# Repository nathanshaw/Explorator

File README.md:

# Explorator Hardware

This repo contains the PCB layout and schematic files for the Explorator genus.

The files included in this repo were created within EAGLE CAD. 
## Repo Structure
PCB
- battery_pack
  - [18500](##Battery-Pack---18500)
  - [18650](##Battery-Pack---18650) 
- [breakout_board](##Explorator-Breakout-PCB)
- mainboard
  - [v1_large_pcb](##Explorator-v1-Mainboard-(large))
  - [v2_small_pcb](##Explorator-v2-Mainboard-(small))

### Repo Files
- .brd files are EAGLE's board files and contain information about the PCB's layout. 
- .sch files are EAGLE's schematic files and contain information about the schematic from which the PCB's are designed.
- .lbr files are EAGLE's library files and contain all the libraries used to create the individual PCB's, there should be a libary file for each folder in the repo. The entire libraries are exported for the battery pack and breakout PCB(including parts not in the design), but for the mainboards only the footprints used in the design are exported to save repo space.
- README.md files accompany each board in the appropiate folder and contains information about manufacturing the PCB, known issues, and other notes
- .png's are included for each board and include the schematic, and the layout of the board.
  - Files that start with "schematic_" are schematic images 
  - Files that start with "layout_" are layout images.
- parts_list.txt is a text file created by EAGLE showing the components used to populate each board. 
- pin_list.txt is a list of all the pin and pad names in the layout and schematic files
- BOM_*.csv is a comma separated list that contains all of the electronic components needed for the PCB (similar to parts_list.txt, but more useful most of the time)
- net_list.txt is a list of all the connections between different nets in the schematic
- CAMOutputs contains two folders, one for the drill file and one for the other gerbers. These outputs were created in EAGLE using the PCBWay_2_layer.cam file at the root level of the PCB folder

Please note, if you do not have access to EAGLE CAD, the easiest way to view these boards is by using an online gerber viewer such as this one provided by [pcbway.com!]<https://www.pcbway.com/project/OnlineGerberViewer.html>. To use this method simply .zip the CAMOutputs folder and drag the compressed .zip file into the browser and an interactive PCB generated from the Gerbers can be viewed. Pretty cool =)

# Repo Contents
The following PCB designs are included in this repo:

## Explorator v1 Mainboard (large)
    
- 99mm diameter
- Teensy 3.2 Microcontroller
- 1x SHTC3 Temperature and Humidity Sensor
- 3x channel of DC motor control
- 9x channels of solenoid control
- 1x power switch
- 1x power input jack
- 2x pots
- 4x buttons

## Explorator v2 Mainboard (small)
- 58mm diameter
- Teensy 3.2 Microcontroller
- 1x channel of DC motor control
- 2x channels of solenoid control
- 2x VEML 6030 Ambient Light Sensors
- 1x SHTC3 Temperature and Humidity Sensor
- 10x WS2813 NeoPixel LEDs
- 1x power switch
- 1x power input jack
- 2x pots
- 2x buttons

## Explorator Breakout PCB
- 40mm diameter
- 10-pin JST connector to mate with mainboard
- 10x WS2813 NeoPixel LEDs
- 1x VEML 6030 Ambient Light Sensor
- 1x TDK ICS-43434 MEMs microphone

## Battery Pack - 18500
- 3x 18500 Lithium Ion Batteries
- Support for routing user controls through PCB
- 2x 100 mil traces for all power connections 
  - providing around 14 amps of current on 2 oz copper PCBs

## Battery Pack - 18650
- 3x 18650 Lithium Ion Batteries
- 1x 100 mil trace for all power connections
  - providing around 7 amps of current on 2 oz copper PCBs

# Related Repos and Work

The Explorator genus firmware is contained in this repo:
- https://github.com/nathanshaw/unified_hss_firmware
More information about this project can be found here: 
- https://nathanvillicanashaw.com/archive

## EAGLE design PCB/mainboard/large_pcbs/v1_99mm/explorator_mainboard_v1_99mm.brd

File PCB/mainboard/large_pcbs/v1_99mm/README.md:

## Explorator Mainboard v1 99mm

## Schematic

## Layout
| Bottom  |  Both  |  Top  |
| ------- | ------- | ------- |
|  |  |  |

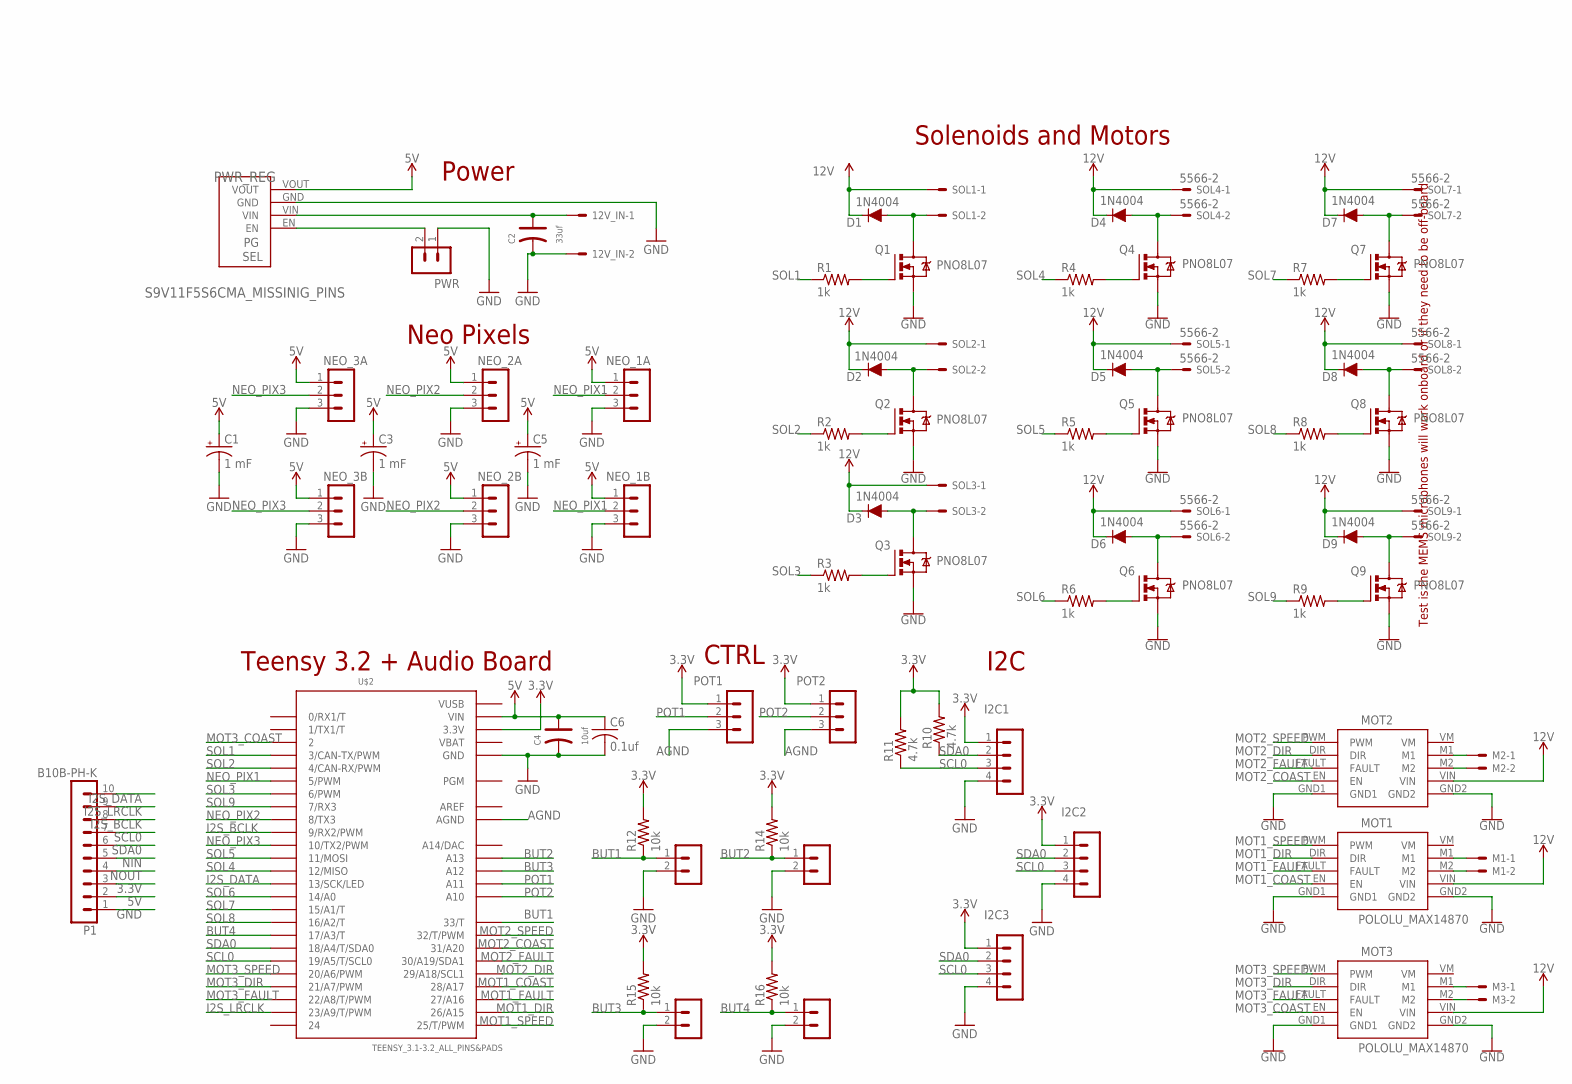
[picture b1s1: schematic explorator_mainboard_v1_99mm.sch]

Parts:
12V_IN: 5566-2
BUT1, BUT2, BUT3, BUT4: B2B-PH-K
C1, C3, C5: 1 mF; UD-10X10_NICHICON
C2: 33uf; PC-D5.3MM
C4: 10uf; PC-D5.3MM
C6: 0.1uf; C2012
D1, D2, D3, D4, D5, D6, D7, D8, D9: 1N4004; DIOAD1138W86L465D235B
I2C1, I2C2, I2C3: B4B-PH-K
M1, M2, M3: 5566-2
MOT1, MOT2, MOT3: POLOLU_MAX14870
NEO_1A, NEO_1B, NEO_2A, NEO_2B, NEO_3A, NEO_3B: B3B-PH-K
P1: B10B-PH-K
POT1, POT2: B3B-PH-K
PWR: B2B-PH-K
PWR_REG: S9V11F5S6CMA_MISSINIG_PINS; S9V11F3S5CMA_MISSING_PINS
Q1, Q2, Q3, Q4, Q5, Q6, Q7, Q8, Q9: PNO8L07; TO220BV
R1, R2, R3, R4, R5, R6, R7, R8, R9: 1k; R0805
R10, R11: 4.7k; R0805
R12, R14, R15, R16: 10k; R0805
SOL1, SOL2, SOL3, SOL4, SOL5, SOL6, SOL7, SOL8, SOL9: 5566-2
U$2: TEENSY_3.1-3.2_ALL_PINS&PADS; TEENSY_3.0-3.2_ALL_PINS_&_PADS

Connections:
3.3V: I2C1.1, I2C2.1, I2C3.1, P1.3, POT1.1, POT2.1, R10.2, R11.2, R12.2, R14.2, R15.2, R16.2, U$2.3.3V, U$2.3.3V1 (3.3V), U$2.3.3V2 (3.3V)
5V: C1.+, C3.+, C4.+, C5.+, C6.1, NEO_1A.1, NEO_1B.1, NEO_2A.1, NEO_2B.1, NEO_3A.1, NEO_3B.1, P1.2, PWR_REG.VOUT, U$2.VIN
12V: 12V_IN.1, C2.+, D1.2 (C), D2.2 (C), D3.2 (C), D4.2 (C), D5.2 (C), D6.2 (C), D7.2 (C), D8.2 (C), D9.2 (C), MOT1.VIN, MOT2.VIN, MOT3.VIN, PWR_REG.VIN, SOL1.1, SOL2.1, SOL3.1, SOL4.1, SOL5.1, SOL6.1, SOL7.1, SOL8.1, SOL9.1
AGND: POT1.3, POT2.3, U$2.AGND
AREF: U$2.AREF
BUT1: BUT1.1, R12.1, U$2.33 (33/T)
BUT2: BUT2.1, R14.1, U$2.A13
BUT3: BUT3.1, R15.1, U$2.A12
BUT4: BUT4.1, R16.1, U$2.17/A3 (17/A3/T)
GND: 12V_IN.2, BUT1.2, BUT2.2, BUT3.2, BUT4.2, C1.-, C2.-, C3.-, C4.-, C5.-, C6.2, I2C1.4, I2C2.4, I2C3.4, MOT1.GND1, MOT1.GND2, MOT2.GND1, MOT2.GND2, MOT3.GND1, MOT3.GND2, NEO_1A.3, NEO_1B.3, NEO_2A.3, NEO_2B.3, NEO_3A.3, NEO_3B.3, P1.1, PWR.1, PWR_REG.GND, Q1.S, Q2.S, Q3.S, Q4.S, Q5.S, Q6.S, Q7.S, Q8.S, Q9.S, U$2.GND, U$2.GND1 (GND), U$2.GND2 (GND)
I2S_BCLK: P1.8, U$2.9 (9/RX2/PWM)
I2S_DATA: P1.10, U$2.13 (13/SCK/LED)
I2S_LRCLK: P1.9, U$2.23/A9 (23/A9/T/PWM)
MOT1_COAST: MOT1.EN, U$2.28 (28/A17)
MOT1_DIR: MOT1.DIR, U$2.26 (26/A15)
MOT1_FAULT: MOT1.FAULT, U$2.27 (27/A16)
MOT1_SPEED: MOT1.PWM, U$2.25 (25/T/PWM)
MOT2_COAST: MOT2.EN, U$2.31 (31/A20)
MOT2_DIR: MOT2.DIR, U$2.29 (29/A18/SCL1)
MOT2_FAULT: MOT2.FAULT, U$2.30 (30/A19/SDA1)
MOT2_SPEED: MOT2.PWM, U$2.32 (32/T/PWM)
MOT3_COAST: MOT3.EN, U$2.2
MOT3_DIR: MOT3.DIR, U$2.21/A7 (21/A7/PWM)
MOT3_FAULT: MOT3.FAULT, U$2.22/A8 (22/A8/T/PWM)
MOT3_SPEED: MOT3.PWM, U$2.20/A6 (20/A6/PWM)
unnamed: Q5.G, R5.2
unnamed: D5.1 (A), Q5.D, SOL5.2
unnamed: M1.2, MOT1.M2
unnamed: Q6.G, R6.2
unnamed: Q2.G, R2.2
unnamed: D6.1 (A), Q6.D, SOL6.2
unnamed: D2.1 (A), Q2.D, SOL2.2
unnamed: M1.1, MOT1.M1
unnamed: PWR.2, PWR_REG.EN
unnamed: Q3.G, R3.2
unnamed: D3.1 (A), Q3.D, SOL3.2
unnamed: Q4.G, R4.2
unnamed: D4.1 (A), Q4.D, SOL4.2
unnamed: M3.2, MOT3.M2
unnamed: M3.1, MOT3.M1
unnamed: Q7.G, R7.2
unnamed: D7.1 (A), Q7.D, SOL7.2
unnamed: Q8.G, R8.2
unnamed: D8.1 (A), Q8.D, SOL8.2
unnamed: Q9.G, R9.2
unnamed: D9.1 (A), Q9.D, SOL9.2
unnamed: Q1.G, R1.2
unnamed: D1.1 (A), Q1.D, SOL1.2
unnamed: M2.2, MOT2.M2
unnamed: M2.1, MOT2.M1
NEO_PIX1: NEO_1A.2, NEO_1B.2, U$2.5 (5/PWM)
NEO_PIX2: NEO_2A.2, NEO_2B.2, U$2.8 (8/TX3)
NEO_PIX3: NEO_3A.2, NEO_3B.2, U$2.10 (10/TX2/PWM)
NIN: P1.5
NOUT: P1.4
POT1: POT1.2, U$2.A11
POT2: POT2.2, U$2.A10
SCL0: I2C1.3, I2C2.3, I2C3.3, P1.7, R11.1, U$2.19/A5 (19/A5/T/SCL0)
SDA0: I2C1.2, I2C2.2, I2C3.2, P1.6, R10.1, U$2.18/A4 (18/A4/T/SDA0)
SOL1: R1.1, U$2.3 (3/CAN-TX/PWM)
SOL2: R2.1, U$2.4 (4/CAN-RX/PWM)
SOL3: R3.1, U$2.6 (6/PWM)
SOL4: R4.1, U$2.12 (12/MISO)
SOL5: R5.1, U$2.11 (11/MOSI)
SOL6: R6.1, U$2.14/A0
SOL7: R7.1, U$2.15/A1 (15/A1/T)
SOL8: R8.1, U$2.16/A2 (16/A2/T)
SOL9: R9.1, U$2.7 (7/RX3)
VBAT: U$2.VBAT
VUSB: U$2.VUSB

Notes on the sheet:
Neo Pixels
I2C
Solenoids and Motors
Teensy 3.2 + Audio Board
Power
CTRL
Test is the MEMS microphones will work onboard or if they need to be off-board

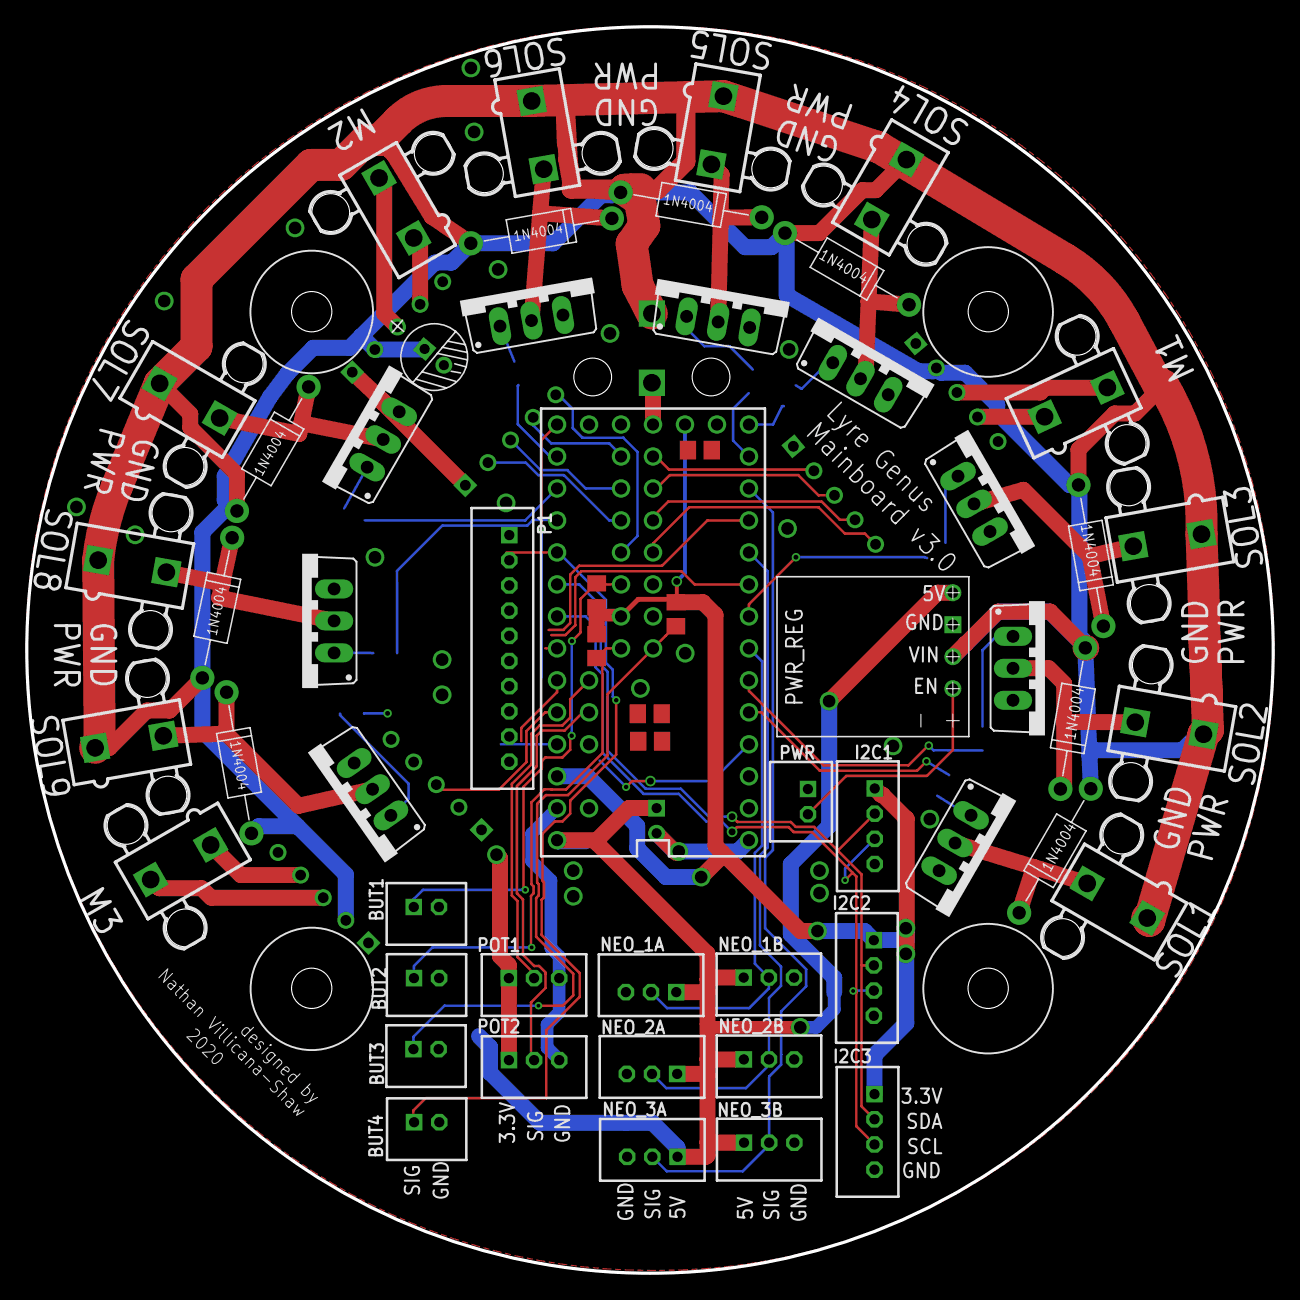
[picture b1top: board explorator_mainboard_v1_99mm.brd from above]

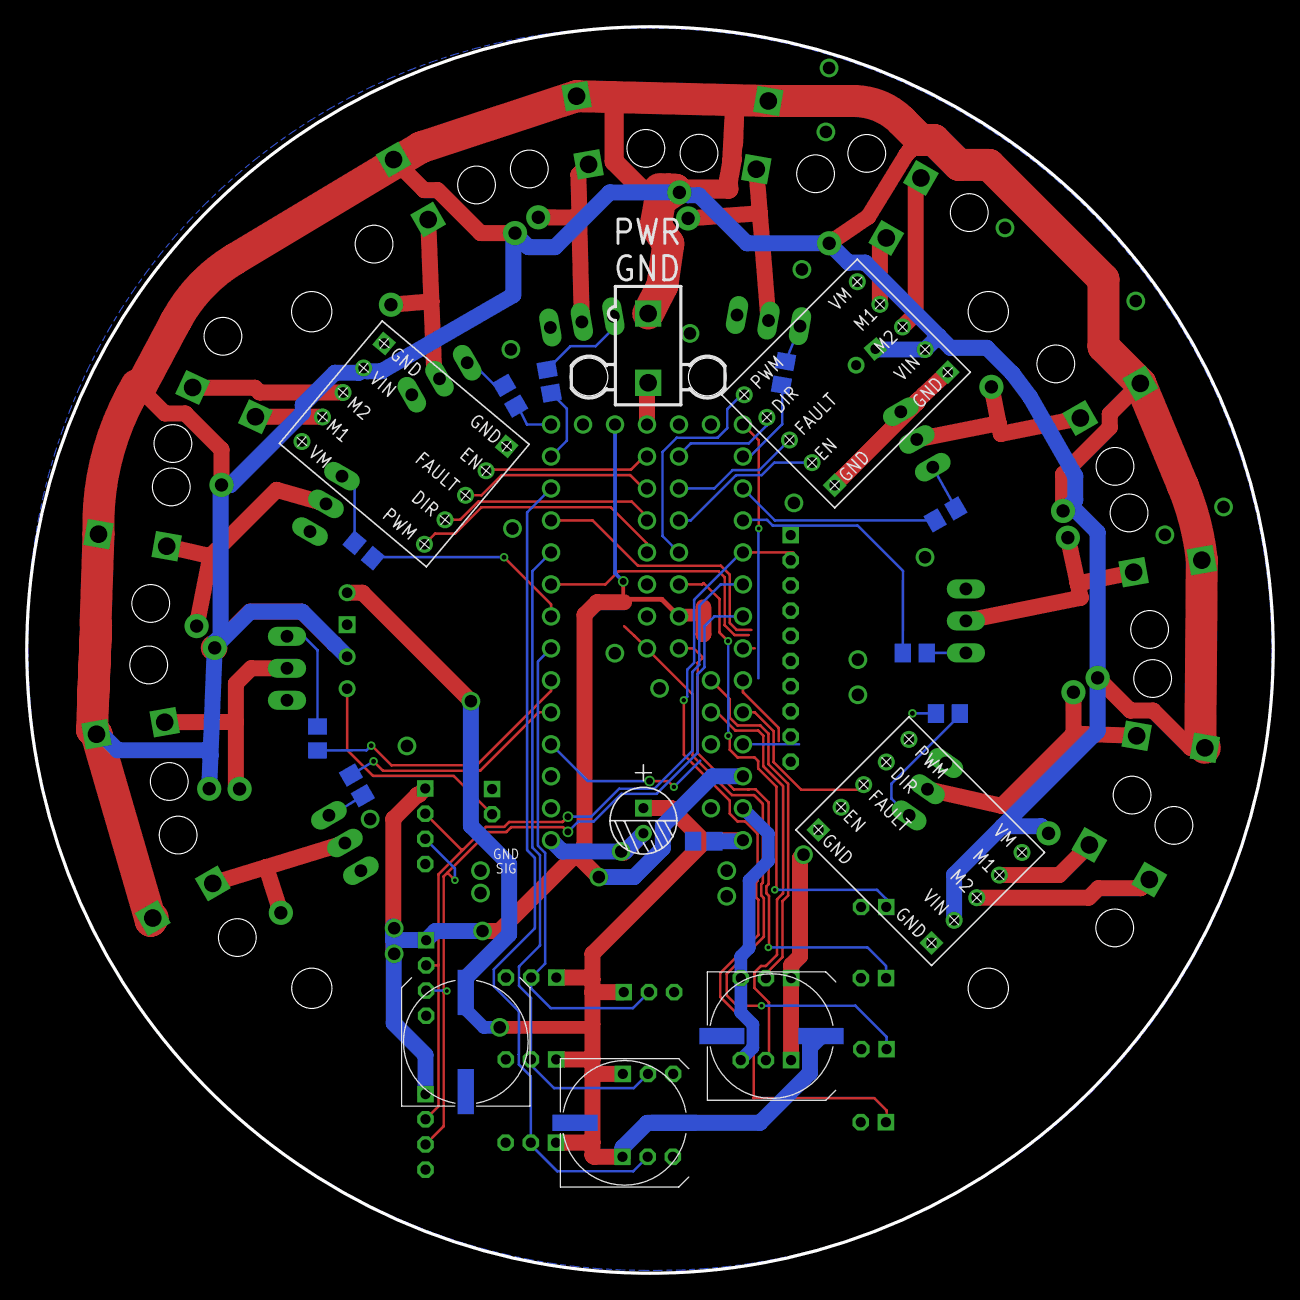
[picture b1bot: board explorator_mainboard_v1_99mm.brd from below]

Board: 2 copper layers, 99.0 x 99.0 mm, 74 parts (18 on the bottom side), 65 nets.

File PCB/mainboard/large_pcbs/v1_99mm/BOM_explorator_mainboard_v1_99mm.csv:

"Qty";"Value";"Device";"Package";"Parts";"Description";"LABEL";"MF";"MPN";"OC_FARNELL";"OC_NEWARK";"POPULARITY";"SPICEPREFIX";"VALUE";
"8";"";"B3B-PH-K";"B3B-PH-K";"NEO_1A, NEO_1B, NEO_2A, NEO_2B, NEO_3A, NEO_3B, POT1, POT2";"HEADER";"";"";"";"";"";"";"";"";
"1";"0.1uf";"C-USC2012";"C2012";"C6";"CAPACITOR, American symbol";"";"";"";"";"";"";"";"";
"3";"1 mF";"CPOL-USUD-10X10";"UD-10X10_NICHICON";"C1, C3, C5";"POLARIZED CAPACITOR, American symbol";"";"";"";"";"";"1";"C";"";
"4";"10k";"R-US_R0805";"R0805";"R12, R14, R15, R16";"RESISTOR, American symbol";"";"";"";"";"";"85";"R";"";
"1";"10uf";"DIP-ALUMINUM-47UF-16V(D5-H7MM)";"PC-D5.3MM";"C4";"302030033";"";"";"KS 100uF/16V";"";"";"";"";"100uf";
"9";"1N4004";"1N4004";"DIOAD1138W86L465D235B";"D1, D2, D3, D4, D5, D6, D7, D8, D9";"";"";"";"";"";"";"";"";"";
"9";"1k";"R-US_R0805";"R0805";"R1, R2, R3, R4, R5, R6, R7, R8, R9";"RESISTOR, American symbol";"";"";"";"";"";"85";"R";"";
"1";"33uf";"DIP-ALUMINUM-47UF-16V(D5-H7MM)";"PC-D5.3MM";"C2";"302030033";"";"";"KS 100uF/16V";"";"";"";"";"100uf";
"2";"4.7k";"R-US_R0805";"R0805";"R10, R11";"RESISTOR, American symbol";"";"";"";"";"";"85";"R";"";
"13";"5566-2";"5566-2";"5566-2";"12V_IN, M1, M2, M3, SOL1, SOL2, SOL3, SOL4, SOL5, SOL6, SOL7, SOL8, SOL9";"Mini FIT connector 2 pol";"";"MOLEX";"";"1822072";"unknown";"";"";"";
"1";"B10B-PH-K";"B10B-PH-K";"B10B-PH-K";"P1";"HEADER";"";"";"";"";"";"";"";"";
"5";"B2B-PH-K";"B2B-PH-K";"B2B-PH-K";"BUT1, BUT2, BUT3, BUT4, PWR";"HEADER";"";"";"";"";"";"";"";"";
"3";"B4B-PH-K";"B4B-PH-K";"B4B-PH-K";"I2C1, I2C2, I2C3";"HEADER";"";"";"";"";"";"";"";"";
"9";"PNO8L07";"IRF540";"TO220BV";"Q1, Q2, Q3, Q4, Q5, Q6, Q7, Q8, Q9";"HEXFET Power MOSFET";"";"";"";"";"";"7";"";"";
"3";"POLOLU_MAX14870";"POLOLU_MAX14870";"POLOLU_MAX14870";"MOT1, MOT2, MOT3";"";"";"";"";"";"";"";"";"";
"1";"S9V11F5S6CMA_MISSINIG_PINS";"S9V11F5S6CMA_MISSINIG_PINS";"S9V11F3S5CMA_MISSING_PINS";"PWR_REG";"";"";"";"";"";"";"";"";"";
"1";"TEENSY_3.1-3.2_ALL_PINS&PADS";"TEENSY_3.1-3.2_ALL_PINS&PADS";"TEENSY_3.0-3.2_ALL_PINS_&_PADS";"U$2";"Footprint for Teensy 3.1 or 3.2 board using all pads and all through-holes. Pads need a 2x7 0.1" SMD header.";"";"";"";"";"";"";"";"";

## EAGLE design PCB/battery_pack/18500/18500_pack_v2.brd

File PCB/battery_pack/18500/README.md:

## Schematic

# PCB Layout

## 18500 Pack V2 Notes
This pack is specifically designed to be placed within a 60mm wide enclosure. 

** IF YOU ARE USING THIS DESIGN FOR YOUR OWN PROJECT, IT IS STRONGLY RECOMMENDED THAT YOU increase the PCB width before manufacturing**

The traces for user controls are EXTREMELY close to the boards edge.

Please keep in mind the expected current requirements for your device
when choosing the copper weight during the manufacturing process. Likewise,
keep in mind the values and current requirements for your physical user
controls (if attached through the PCB).
- The PWR traces for the board are 100 mil thick and are doubled up for all connections to increase current capacity.
- This means that if the copper thickness is 1 oz. the board can withstand continuous currents of around 4.7 Amps per-trace or 9.4 amps total.
- If the copper thickness is increased to 2 oz the board can withstand around 7.7 amps per trace, or 15.4 amps total
- Both of these numbers are very rough estimates that are assuming an ambient temperature of 25 C, and a maximum trace temperature ride of 10 C
- The PCB Trace Width Calculator by 4pcb.com is a great tool to help with these calculators: [Try Their Tool Here!]<https://www.4pcb.com/trace-width-calculator.html>

### Notes for Future Revisions
- Move logic traces away from side of PCB
- Consider combining GND and PWR for user controls to reduce traces i
  - (must investigate the EE implication of this)

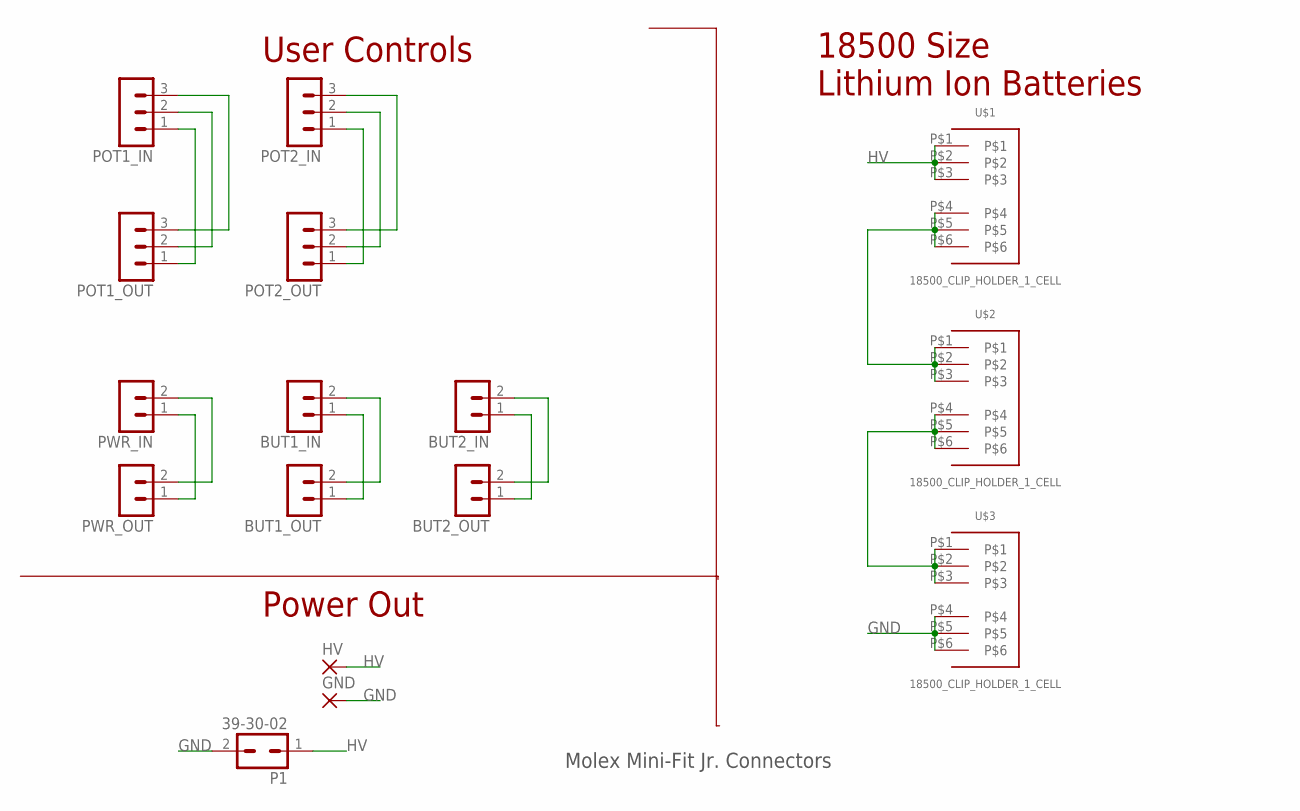
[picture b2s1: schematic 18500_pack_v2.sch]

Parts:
BUT1_IN, BUT1_OUT, BUT2_IN, BUT2_OUT: B2B-PH-K
GND: 2,54/1,1
HV: 2,54/1,1
P1: 39-30-02; 39-30-?02?
POT1_IN, POT1_OUT, POT2_IN, POT2_OUT: B3B-PH-K
PWR_IN: B2B-PH-K
PWR_OUT: B2B-PH-K
U$1, U$2, U$3: 18500_CLIP_HOLDER_1_CELL; 3PINBATTERY_CLIP_1_CELL_18500

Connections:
GND: GND.1, P1.2, U$3.P$4, U$3.P$5, U$3.P$6
HV: HV.1, P1.1, U$1.P$1, U$1.P$2, U$1.P$3
unnamed: U$1.P$4, U$1.P$5, U$1.P$6, U$2.P$1, U$2.P$2, U$2.P$3
unnamed: U$2.P$4, U$2.P$5, U$2.P$6, U$3.P$1, U$3.P$2, U$3.P$3
unnamed: PWR_IN.2, PWR_OUT.2
unnamed: PWR_IN.1, PWR_OUT.1
unnamed: BUT1_IN.2, BUT1_OUT.2
unnamed: BUT1_IN.1, BUT1_OUT.1
unnamed: BUT2_IN.2, BUT2_OUT.2
unnamed: BUT2_IN.1, BUT2_OUT.1
unnamed: POT1_IN.1, POT1_OUT.1
unnamed: POT1_IN.2, POT1_OUT.2
unnamed: POT1_IN.3, POT1_OUT.3
unnamed: POT2_IN.1, POT2_OUT.1
unnamed: POT2_IN.2, POT2_OUT.2
unnamed: POT2_IN.3, POT2_OUT.3

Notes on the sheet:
18500 Size Lithium Ion Batteries
User Controls
Power Out
Molex Mini-Fit Jr. Connectors

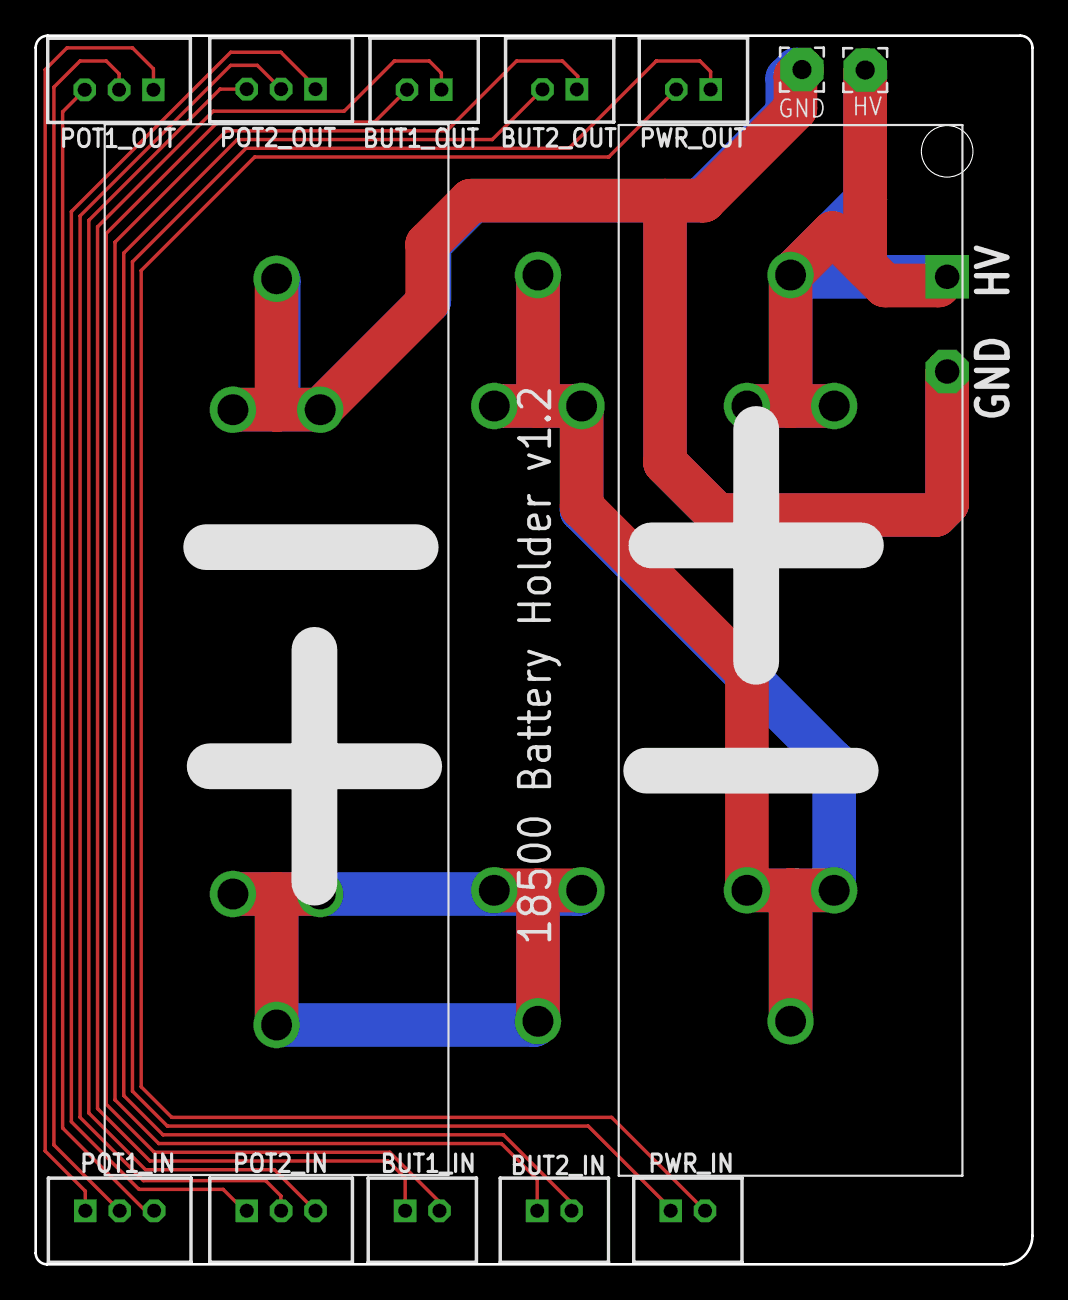
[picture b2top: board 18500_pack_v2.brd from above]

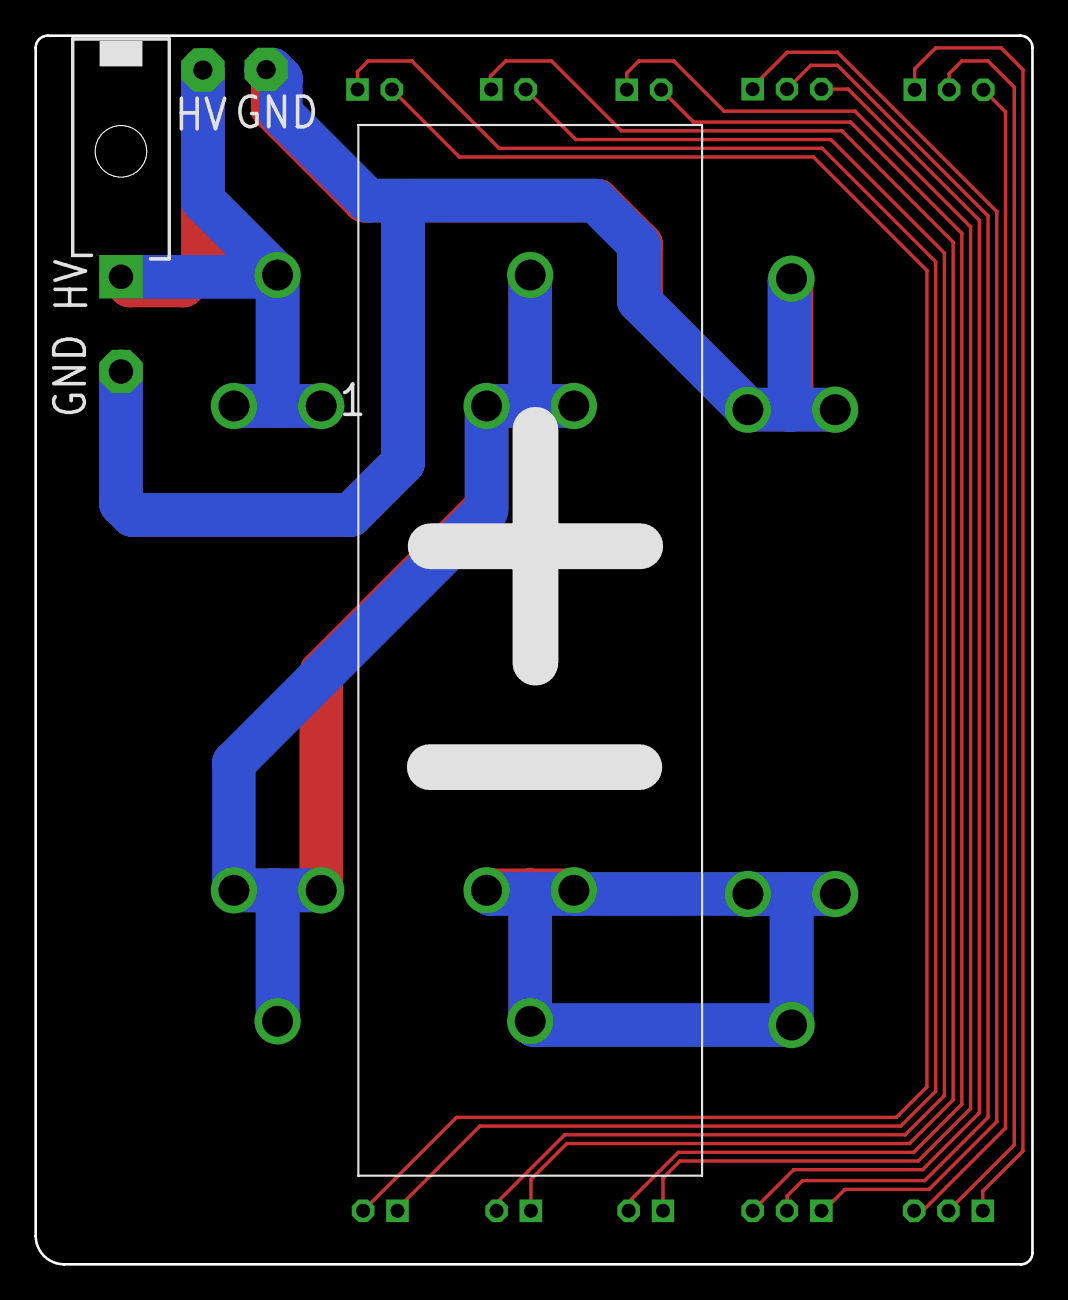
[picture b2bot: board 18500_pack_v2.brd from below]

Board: 2 copper layers, 58.0 x 71.5 mm, 16 parts (2 on the bottom side), 16 nets.

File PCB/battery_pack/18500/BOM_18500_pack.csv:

"Qty";"Value";"Device";"Package";"Parts";"Description";"LABEL";"POPULARITY";
"2";"";"2,54/1,1";"2,54/1,1";"GND, HV";"THROUGH-HOLE PAD";"";"6";
"3";"18500_CLIP_HOLDER_1_CELL";"18500_CLIP_HOLDER_1_CELL";"3PINBATTERY_CLIP_1_CELL_18500";"U$1, U$2, U$3";"";"";"";
"1";"39-30-02?";"39-30-02?";"39-30-?02?";"P1";"HEADER";"";"";
"6";"B2B-PH-K";"B2B-PH-K";"B2B-PH-K";"BUT1_IN, BUT1_OUT, BUT2_IN, BUT2_OUT, PWR_IN, PWR_OUT";"HEADER";"";"";
"4";"B3B-PH-K";"B3B-PH-K";"B3B-PH-K";"POT1_IN, POT1_OUT, POT2_IN, POT2_OUT";"HEADER";"";"";

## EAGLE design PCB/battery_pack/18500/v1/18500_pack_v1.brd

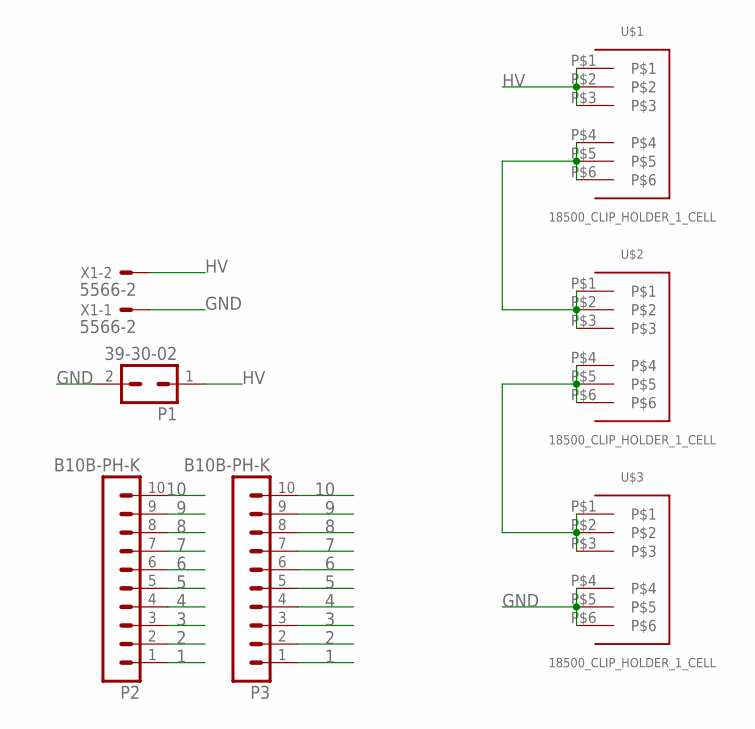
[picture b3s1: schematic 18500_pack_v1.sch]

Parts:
P1: 39-30-02; 39-30-?02?
P2, P3: B10B-PH-K
U$1, U$2, U$3: 18500_CLIP_HOLDER_1_CELL; 3PINBATTERY_CLIP_1_CELL_18500
X1: 5566-2

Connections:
1: P2.1, P3.1
2: P2.2, P3.2
3: P2.3, P3.3
4: P2.4, P3.4
5: P2.5, P3.5
6: P2.6, P3.6
7: P2.7, P3.7
8: P2.8, P3.8
9: P2.9, P3.9
10: P2.10, P3.10
GND: P1.2, U$3.P$4, U$3.P$5, U$3.P$6, X1.1
HV: P1.1, U$1.P$1, U$1.P$2, U$1.P$3, X1.2
unnamed: U$1.P$4, U$1.P$5, U$1.P$6, U$2.P$1, U$2.P$2, U$2.P$3
unnamed: U$2.P$4, U$2.P$5, U$2.P$6, U$3.P$1, U$3.P$2, U$3.P$3

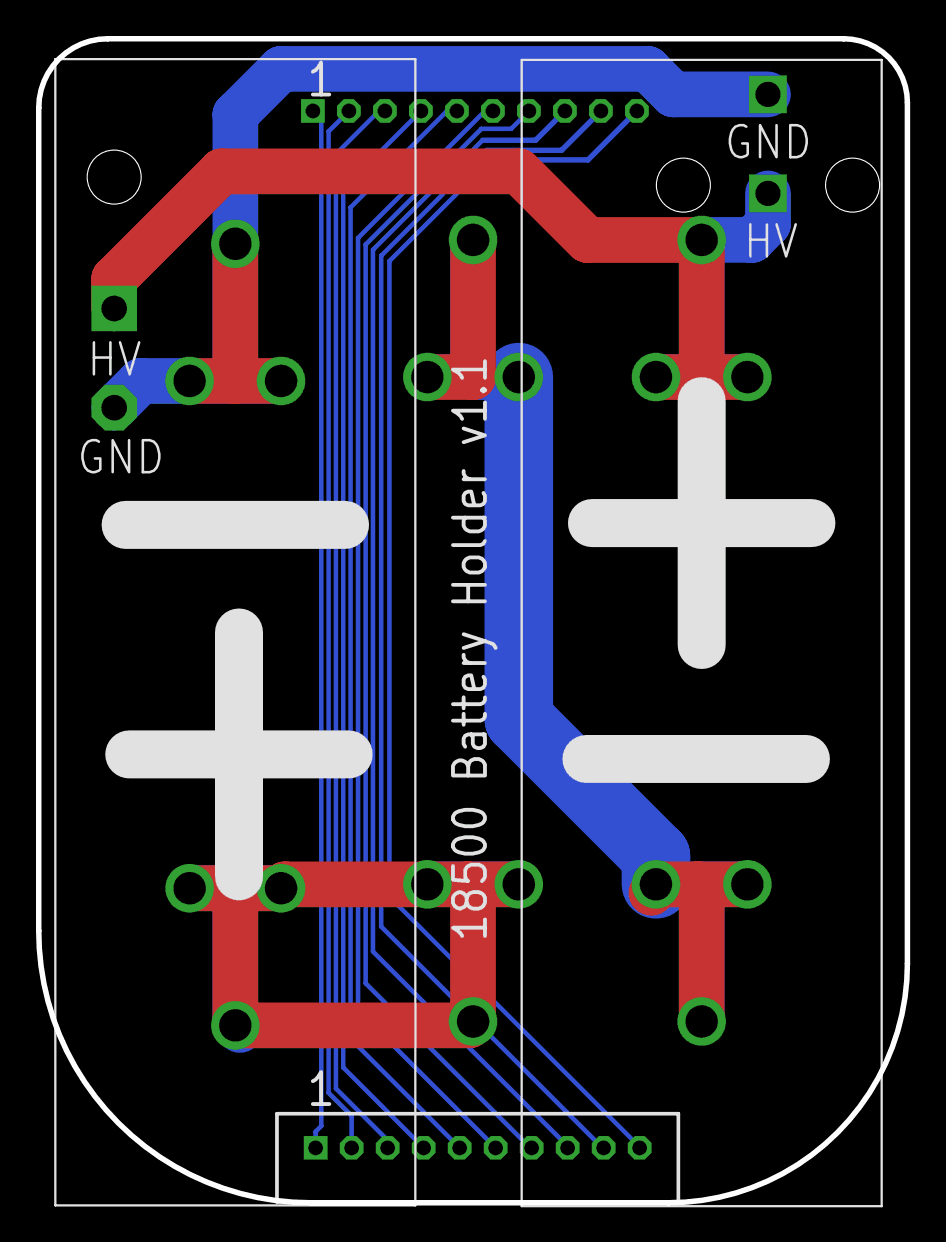
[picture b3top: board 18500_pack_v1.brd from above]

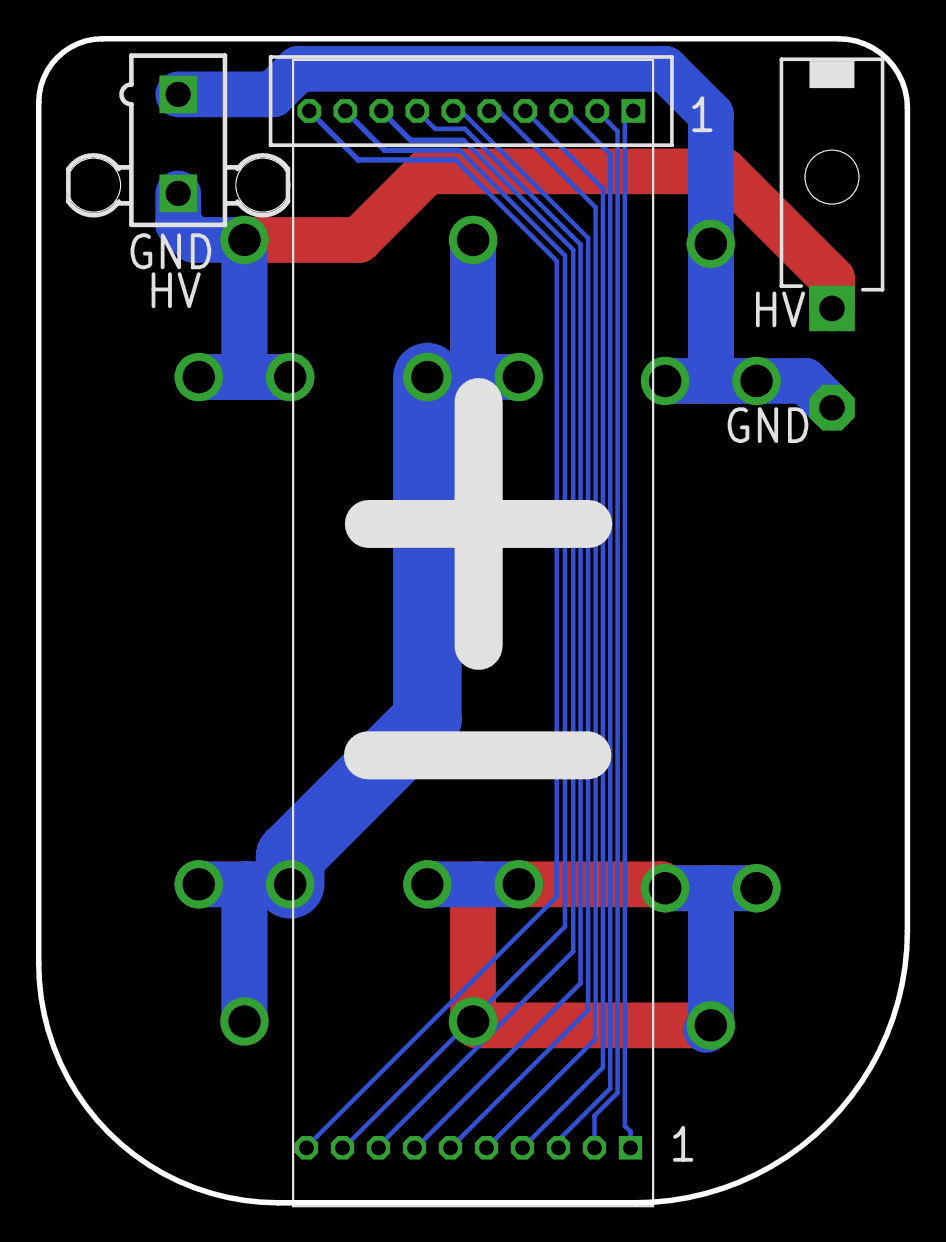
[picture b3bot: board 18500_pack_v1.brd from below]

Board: 2 copper layers, 48.3 x 64.7 mm, 7 parts (4 on the bottom side), 14 nets.

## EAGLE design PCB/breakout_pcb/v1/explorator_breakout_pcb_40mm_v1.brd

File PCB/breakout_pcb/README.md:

## Explorator Breakout PCB
This PCB can be used in tandem with the Explorator mainboard PCBs
To provide environmental sensing capability.

### Notes
- The PCB provides footprints for two different types of ambient light sensors to allow the user to select whichever sensor they have in stock or is best suited for the project. The foootprints provided are for the 
- - VEML6030 sensor 
- - VEML7700 sensor

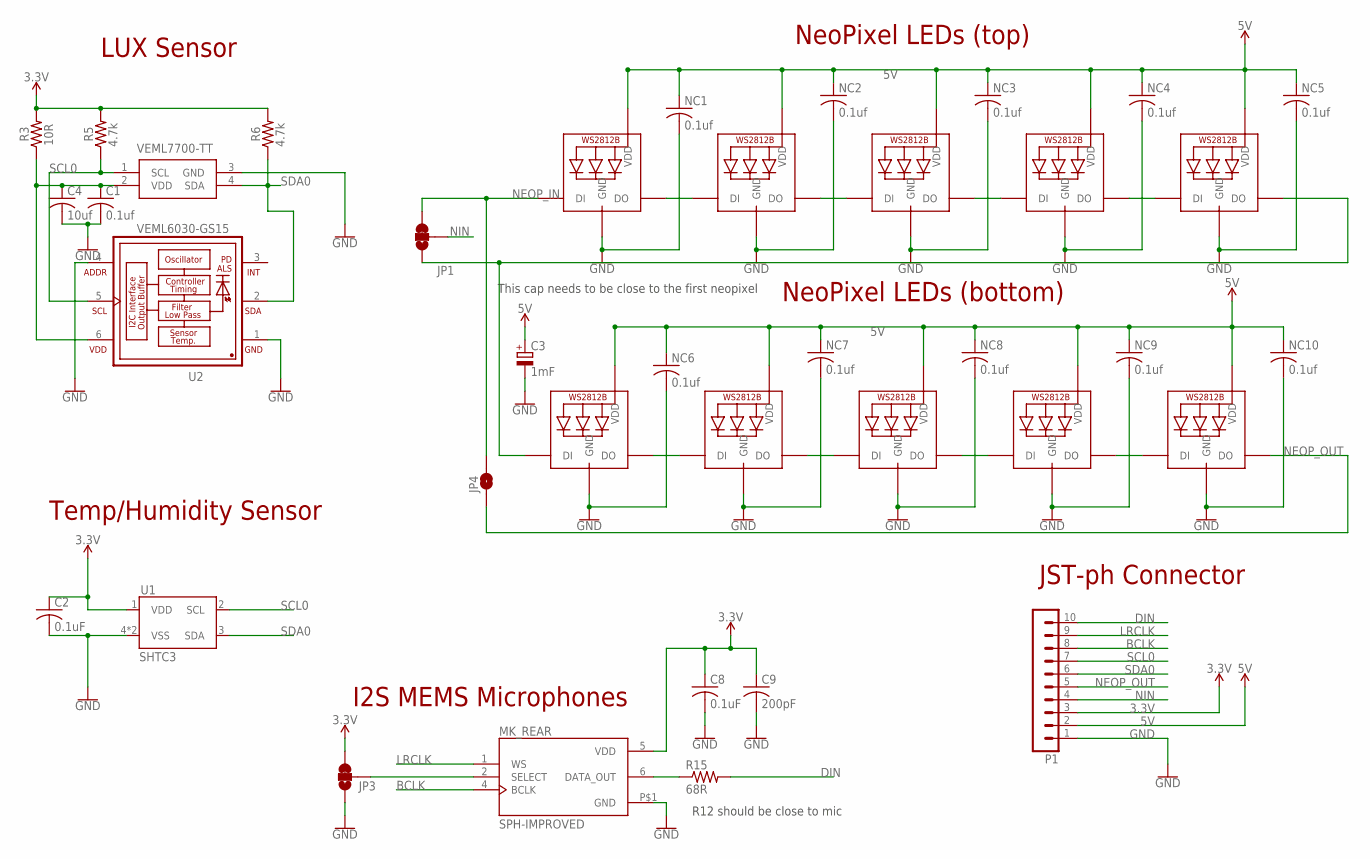
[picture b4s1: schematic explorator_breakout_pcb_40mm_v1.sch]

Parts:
C1: 0.1uf; C0805
C2, C8: 0.1uF; C0805
C3: 1mF; 153CLV-1012
C4: 10uf; C0805
C9: 200pF; C0805
JP1, JP3: JUMPER-SMT_3_1-NC_TRACE_SILK; SMT-JUMPER_3_1-NC_TRACE_SILK
JP4: JUMPER-SMT_2_NO_SILK; SMT-JUMPER_2_NO_SILK
MK_REAR: SPH-IMPROVED; MIC_SPH0645LM4H-B_LARGER_RING
NC1, NC2, NC3, NC4, NC5, NC6, NC7, NC8, NC9, NC10: 0.1uf; C0805
NEO_01, NEO_02, NEO_03, NEO_04, NEO_05, NEO_06, NEO_07, NEO_08, NEO_09, NEO_10: WS2812; WS2812B
P1: B10B-PH-K
R3: 10R; R0805
R5, R6: 4.7k; R0805
R15: 68R; R0805
U1: SHTC3
U2: VEML6030-GS15; VISHAY_VEML6030_2X2X0.87
VEML_F: VEML7700-TT; VEML7700

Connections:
3.3V: C2.1, C8.1, C9.1, JP3.3, MK_REAR.5 (VDD), P1.3, R3.2, R5.2, R6.2, U1.1 (VDD)
5V: C3.+, NC1.1, NC2.1, NC3.1, NC4.1, NC5.1, NC6.1, NC7.1, NC8.1, NC9.1, NC10.1, NEO_01.1-VDD (VDD), NEO_02.1-VDD (VDD), NEO_03.1-VDD (VDD), NEO_04.1-VDD (VDD), NEO_05.1-VDD (VDD), NEO_06.1-VDD (VDD), NEO_07.1-VDD (VDD), NEO_08.1-VDD (VDD), NEO_09.1-VDD (VDD), NEO_10.1-VDD (VDD), P1.2
BCLK: MK_REAR.4 (BCLK), P1.8
DIN: P1.10, R15.2
GND: C1.2, C2.2, C3.-, C4.2, C8.2, C9.2, JP3.1, MK_REAR.P$1 (GND), NC1.2, NC2.2, NC3.2, NC4.2, NC5.2, NC6.2, NC7.2, NC8.2, NC9.2, NC10.2, NEO_01.3-GND (GND), NEO_02.3-GND (GND), NEO_03.3-GND (GND), NEO_04.3-GND (GND), NEO_05.3-GND (GND), NEO_06.3-GND (GND), NEO_07.3-GND (GND), NEO_08.3-GND (GND), NEO_09.3-GND (GND), NEO_10.3-GND (GND), P1.1, U1.4 (VSS), U1.5 (VSS), U2.1 (GND), U2.4 (ADDR), VEML_F.3 (GND)
LRCLK: MK_REAR.1 (WS), P1.9
unnamed: C1.1, C4.1, R3.1, U2.6 (VDD), VEML_F.2 (VDD)
unnamed: JP1.1, NEO_05.2-DOUT (DO), NEO_06.4-DIN (DI)
unnamed: NEO_02.2-DOUT (DO), NEO_03.4-DIN (DI)
unnamed: NEO_09.2-DOUT (DO), NEO_10.4-DIN (DI)
unnamed: JP3.2, MK_REAR.2 (SELECT)
unnamed: NEO_07.2-DOUT (DO), NEO_08.4-DIN (DI)
unnamed: NEO_04.2-DOUT (DO), NEO_05.4-DIN (DI)
unnamed: NEO_08.2-DOUT (DO), NEO_09.4-DIN (DI)
unnamed: NEO_03.2-DOUT (DO), NEO_04.4-DIN (DI)
unnamed: MK_REAR.6 (DATA_OUT), R15.1
NEOP_IN: JP1.3, JP4.2, NEO_01.4-DIN (DI)
NEOP_OUT: JP4.1, NEO_10.2-DOUT (DO), P1.5
NEO_P1: NEO_01.2-DOUT (DO), NEO_02.4-DIN (DI)
NEO_P2: NEO_06.2-DOUT (DO), NEO_07.4-DIN (DI)
NIN: JP1.2, P1.4
SCL0: P1.7, R5.1, U1.2 (SCL), U2.5 (SCL), VEML_F.1 (SCL)
SDA0: P1.6, R6.1, U1.3 (SDA), U2.2 (SDA), VEML_F.4 (SDA)

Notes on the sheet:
I2S MEMS Microphones
LUX Sensor
NeoPixel LEDs (top)
4.7k
R12 should be close to mic
10R
This cap needs to be close to the first neopixel
Temp/Humidity Sensor
NeoPixel LEDs (bottom)
JST-ph Connector

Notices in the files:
parts and their libraries:
con-molex-mini-fit: Copyright (C) 2011, Bob Starr
con-jst-ph: Copyright (C) 2016, Bob Starr
SparkFun-Jumpers: Licensing: Creative Commons ShareAlike 4.0 International - https://creativecommons.org/licenses/by-sa/4.0
